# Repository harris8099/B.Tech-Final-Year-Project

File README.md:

# ESP32 Smart Motor Monitor — PCB Design

> KiCad schematic and PCB layout for an ESP32-based industrial motor monitoring and protection system.

---

## Quick Links

| Resource | Link |
|---|---|
| 🌐 Live cloud dashboard | [motor-frontend-psi.vercel.app](https://motor-frontend-psi.vercel.app/) |
| 🖥️ ESP32 local website (demo) | [harris8099.github.io/Motor-Website](https://harris8099.github.io/Motor-Website/index.html) |
| 📦 ESP32 firmware (this repo) | [github.com/harris8099/Final-Year-Project](https://github.com/harris8099/Final-Year-Project) |
| 🎓 PCB schematic and layout | [github.com/harris8099/B.Tech-Final-Year-Project](https://github.com/harris8099/B.Tech-Final-Year-Project) |
| 🖼️ Frontend repository | [github.com/harris8099/Motor-frontend](https://github.com/harris8099/Motor-frontend) |
| ⚙️ Backend repository | [github.com/harris8099/Motor-backend](https://github.com/harris8099/Motor-backend) |
| 📐 Project diagrams & architecture | [github.com/harris8099/Motor-project-Diagram](https://github.com/harris8099/Motor-project-Diagram) |
| 📱 Alternative Bluetooth approach | [harris8099.github.io/Bluetooth-Motor-app](https://harris8099.github.io/Bluetooth-Motor-app/) |

---

## Schematic Overview

Motor Connector Pinout

ADXL345 Sensitivity Reference

## Project Files

| File | Description |
|---|---|
| `ESP32_Smart_Motor_Project.kicad_sch` | Main schematic |
| `overall.kicad_sch` | Top-level/hierarchical schematic |
| `ESP32_Smart_Motor_Project.kicad_pcb` | PCB layout |
| `ESP32_Smart_Motor_Project.kicad_pro` | KiCad project file |
| `Symbol_Lib.kicad_sym` | Custom component symbol library |
| `sch.pdf` | Schematic PDF export |
| `Components_Links.xlsx` | Full BOM with supplier links |
| `ESP32.jpg` | ESP32 module reference image |
| `MOTOR Pins.png` | Motor connector pinout reference |
| `Vibration sensitivity.png` | ADXL345 sensitivity reference |
| `pcbway_production/` | Gerber files for PCB fabrication (PCBWay) |
| `plots/` | Schematic and layout plot exports |
| `Datasheet/` | Component datasheets |

---

## Schematic Overview

The schematic is divided into functional blocks:

### 1. Microcontroller — ESP32-WROOM-32
- Dual-core Xtensa LX6 @ 240 MHz
- 4MB Flash, 520KB SRAM
- On-board Wi-Fi 802.11 b/g/n
- USB-to-UART via CP2102/CH340 for programming and debug
- 3.3V operation with on-board LDO

### 2. Power Supply
- Input: 5V DC from external adapter or USB
- ESP32 powered via 3.3V LDO (AMS1117-3.3 or equivalent)
- Decoupling capacitors on all supply rails (100nF ceramic + 10µF electrolytic)
- Separate power domains for analog sensors and digital logic

### 3. PZEM-004T v3.0 — Power Measurement
- Interface: UART2 (TX → GPIO17, RX → GPIO16)
- Measures: Voltage (80–260V AC), Current (0–100A), Active Power, Energy (kWh), Frequency, Power Factor
- CT (current transformer) clamp around motor live wire
- Isolated from ESP32 logic via UART optocoupler or direct UART (module has internal isolation)
- Baud rate: 9600, 8N1

### 4. DS18B20 — Temperature Sensor
- Interface: 1-Wire (single GPIO)
- 4.7kΩ pull-up resistor on data line to 3.3V (**required**)
- Measures motor winding temperature: –55°C to +125°C, ±0.5°C accuracy
- Waterproof probe variant recommended for motor surface mounting

### 5. ADXL345 — Vibration / Acceleration Sensor
- Interface: I2C (SDA, SCL)
- I2C address: 0x53 (SDO pulled low) or 0x1D (SDO high)
- 4.7kΩ pull-up resistors on SDA and SCL lines
- Range: ±16g, Resolution: 3.9mg/LSB at full range
- Tap detection configured via firmware (threshold, duration, axes)
- Decoupling: 100nF on VCC pin

### 6. Hall Effect Sensor — RPM Measurement
- Interface: GPIO (interrupt-driven)
- GPIO5 configured as input with interrupt on rising edge
- Magnet mounted on motor shaft; sensor detects each revolution
- Pull-up resistor on signal line
- 100nF ceramic capacitor from signal to GND for EMI suppression

### 7. Relay Module — Motor Contactor
- Interface: GPIO (active-low)
- Drives motor contactor coil via relay
- Flyback diode (1N4007) across relay coil for back-EMF protection
- Optocoupler isolation between ESP32 logic and relay coil circuit
- LED indicator for relay state

### 8. Buzzer — Fault Alert
- Interface: GPIO (PWM capable)
- Active buzzer driven via NPN transistor (BC547 or 2N2222)
- 1kΩ base resistor, 10kΩ pull-down to prevent ghost triggering at boot
- Sounds on fault latch

### 9. TFT Display
- Interface: SPI
- CS, DC, RST, BLK connected to dedicated GPIOs
- Backlight PWM dimming capable
- Displays real-time sensor values and fault status locally

---

## Pin Assignment

| GPIO | Function | Direction | Notes |
|---|---|---|---|
| GPIO5 | Hall sensor | Input (IRQ) | 100nF cap to GND |
| GPIO16 | PZEM004T RX | Input | UART2 |
| GPIO17 | PZEM004T TX | Output | UART2 |
| GPIO21 | I2C SDA | Bidirectional | 4.7kΩ pull-up |
| GPIO22 | I2C SCL | Output | 4.7kΩ pull-up |
| GPIO26 | Relay | Output | Active-low |
| GPIO27 | Buzzer | Output | Via NPN transistor |
| 1-Wire GPIO | DS18B20 | Bidirectional | 4.7kΩ pull-up |
| SPI GPIOs | TFT Display | Output | CS/DC/RST/BLK |
| GPIO36 | TFT Button | Input | menu_next (ADC capable) |
| EN / IO0 | Boot control | — | Boot strapping pins |

---

## PCB Design Notes

### Layer Stack
- **2-layer PCB** (standard FR4, 1.6mm thickness)
- Top layer: signal routing + components
- Bottom layer: ground plane + power traces

### Design Rules
- Minimum trace width: 0.25mm (signal), 1.0mm (power), 2.0mm (5V/relay)
- Minimum clearance: 0.2mm
- Via drill: 0.8mm, via pad: 1.6mm
- Board outline: defined in Edge.Cuts layer

### Layout Guidelines Applied
- ESP32 module antenna area kept clear of copper pours and traces
- PZEM UART traces kept short and away from relay switching traces
- I2C pull-up resistors placed close to SDA/SCL pins
- DS18B20 pull-up resistor placed close to connector
- Relay and motor-side traces physically separated from ESP32 signal area
- Decoupling capacitors placed as close as possible to IC power pins
- Ground plane on bottom layer with stitching vias

### Production Files (pcbway_production/)
Standard Gerber outputs for PCBWay fabrication:
- `*.GTL` — Top copper
- `*.GBL` — Bottom copper
- `*.GTS` — Top solder mask
- `*.GBS` — Bottom solder mask
- `*.GTO` — Top silkscreen
- `*.GBO` — Bottom silkscreen
- `*.GKO` — Board outline
- `*.DRL` — Drill file (Excellon)

---

## Bill of Materials (BOM)

Full BOM with supplier links is in `Components_Links.xlsx`. Key components:

| Ref | Component | Value / Part | Package |
|---|---|---|---|
| U1 | ESP32-WROOM-32 | ESP32-WROOM-32D | Module |
| U2 | PZEM-004T | v3.0 | Module |
| U3 | ADXL345 | ADXL345BCCZ | LGA-14 |
| U4 | DS18B20 | DS18B20 | TO-92 / Probe |
| U5 | Voltage Regulator | AMS1117-3.3 | SOT-223 |
| Q1 | NPN Transistor | BC547 / 2N2222 | TO-92 |
| RL1 | Relay | 5V SPDT 10A | Through-hole |
| D1 | Flyback Diode | 1N4007 | DO-41 |
| R1 | DS18B20 Pull-up | 4.7kΩ | 0402 |
| R2, R3 | I2C Pull-up | 4.7kΩ | 0402 |
| R4 | Buzzer Base | 1kΩ | 0402 |
| R5 | Buzzer Pull-down | 10kΩ | 0402 |
| R6 | Hall Pull-up | 10kΩ | 0402 |
| C1–C5 | Decoupling | 100nF | 0402 |
| C6, C7 | Bulk Decoupling | 10µF | 0805 |
| BZ1 | Buzzer | Active 5V | Through-hole |
| J1 | Motor Connector | Screw terminal 3P | 5.08mm pitch |
| J2 | PZEM Connector | JST/Screw 4P | — |
| J3 | TFT Connector | Pin header 8P | 2.54mm |
| J4 | USB / Power | Micro-USB / DC jack | — |
| HALL1 | Hall Sensor | SS49E / A3144 | TO-92 |
| TFT1 | TFT Display | ST7789 / ILI9341 | Module |

---

## Schematic PDF

See [`sch.pdf`](sch.pdf) for the full schematic with all net labels, component values, and reference designators.

---

## Tools Used

| Tool | Version | Purpose |
|---|---|---|
| KiCad | 7.x / 8.x | Schematic capture + PCB layout |
| PCBWay | — | PCB fabrication |
| KiCad PDF Plotter | — | `sch.pdf` export |

---

## Related Repositories

| Repository | Description |
|---|---|
| [Final-Year-Project](https://github.com/harris8099/Final-Year-Project) | ESP32 firmware (ESP-IDF) |
| [Motor-frontend](https://github.com/harris8099/Motor-frontend) | React cloud dashboard |
| [Motor-backend](https://github.com/harris8099/Motor-backend) | FastAPI + PostgreSQL backend |
| [Motor-project-Diagram](https://github.com/harris8099/Motor-project-Diagram) | System architecture diagrams |

## Live Deployments

| Deployment | URL |
|---|---|
| Cloud dashboard | https://motor-frontend-psi.vercel.app/ |
| ESP32 local website demo | https://harris8099.github.io/Motor-Website/index.html |

---

## Author

**Harshil Suthar**

[LinkedIn](https://www.linkedin.com/in/harshil-suthar-942307249/) · [GitHub](https://github.com/harris8099) · [Portfolio](https://harris8099.github.io/Portfolio-2.0/)

---

*Public Domain (CC0). No warranty expressed or implied.*

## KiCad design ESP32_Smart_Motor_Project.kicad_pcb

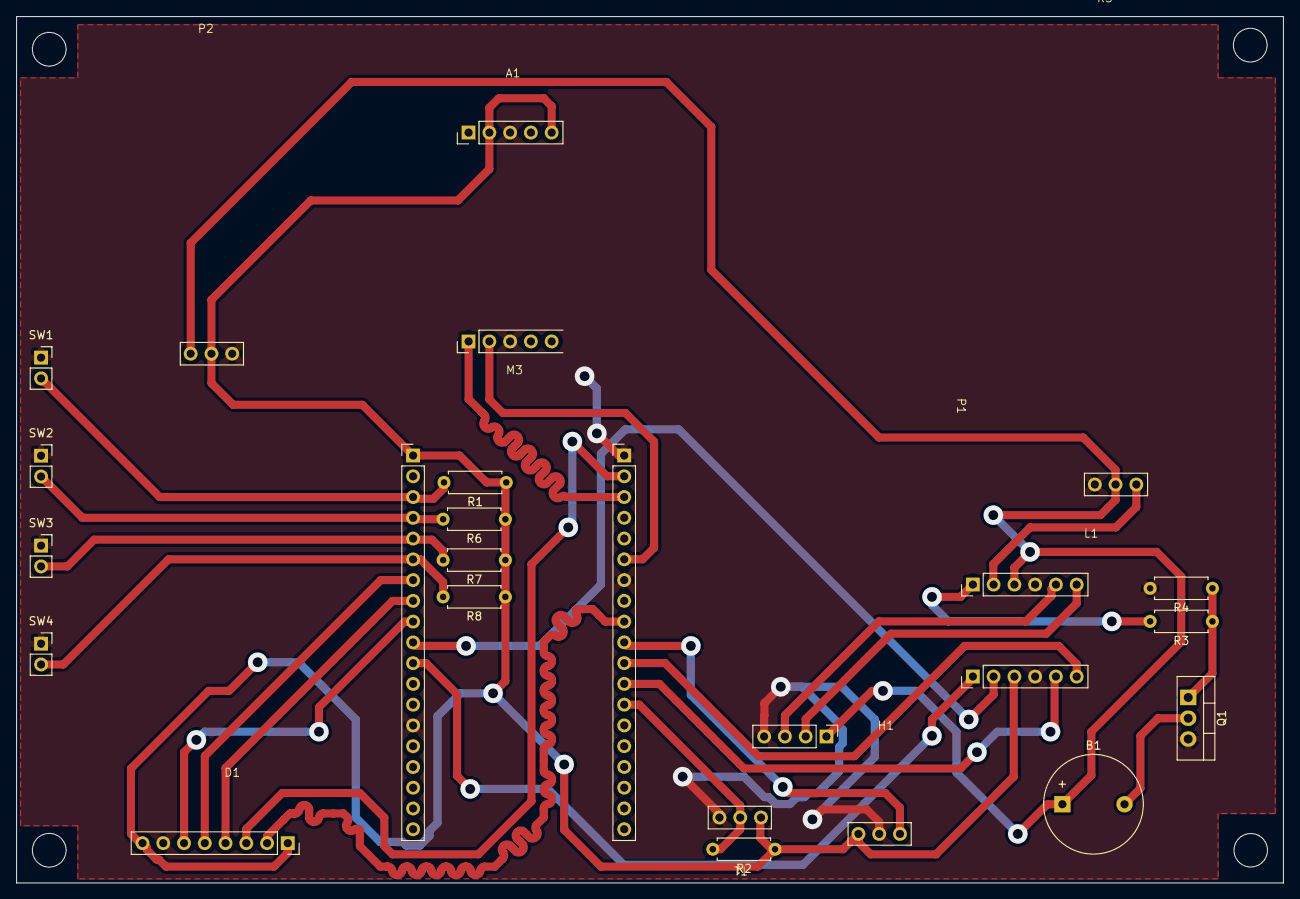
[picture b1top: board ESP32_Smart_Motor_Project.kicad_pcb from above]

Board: 2 copper layers, 155.0 x 106.0 mm, 22 parts (0 on the bottom side), 26 nets.

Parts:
A1: ADXL345
B1: Buzzer_12x9.5RM7.6
D1: TFT_display
H1: Hall_sensor
L1: Logic_convertor
M3: ESP32
P1: PZEM_004T
P2: Power_supply
Q1: IRLZ34N; TO-220-3_Vertical
R1, R4, R6, R7, R8: 10K; R_Axial_DIN0207_L6.3mm_D2.5mm_P7.62mm_Horizontal
R2: 4.7K; R_Axial_DIN0207_L6.3mm_D2.5mm_P7.62mm_Horizontal
R3: 100ohm; R_Axial_DIN0207_L6.3mm_D2.5mm_P7.62mm_Horizontal
R5: Relay
SW1, SW2, SW3, SW4: SW_Push; PinSocket_1x02_P2.54mm_Vertical
T1: DS18B20

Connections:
/3V3: A1.2 (3V3), A1.5 (CS), D1.1 (LED), D1.8 (3.3V), H1.1 (3V3), L1.9 (LV), M3.20 (3.3V), P2.2 (3V3), R1.1, R2.1, R6.1, R7.1, R8.1, T1.1 (3V3)
/5V: B1.1 (SIG), L1.3 (HV), P1.1 (5V), P2.1 (5V), R5.2 (5V)
/GND: A1.3 (GND), A1.8 (SDO), D1.7 (GND), H1.2 (GND), L1.4 (GND), L1.10 (GND), M3.1 (GND), M3.7 (GND), M3.33 (GND), P1.4 (GND), P2.3 (GND), Q1.3 (S), R4.2, R5.1 (GND), SW1.1, SW2.1, SW3.1, SW4.1, T1.3 (GND)
/GPIO4: M3.13 (GPIO4), R2.2, T1.2 (SIG)
/GPIO5: H1.3 (DO), M3.10 (GPIO5)
/GPIO16: L1.11 (LV3), M3.12 (GPIO16)
/GPIO17: L1.12 (LV4), M3.11 (GPIO17)
/GPIO18: D1.2 (SCK), M3.9 (GPIO18)
/GPIO21: A1.7 (SDA), M3.6 (GPIO21)
/GPIO22: A1.6 (SCL), M3.3 (GPIO22)
/GPIO23: D1.3 (SDA), M3.2 (GPIO23)
/GPIO25: D1.6 (CS), M3.28 (GPIO25)
/GPIO26: L1.8 (LV2), M3.29 (GPIO26)
/GPIO27: L1.7 (LV1), M3.30 (GPIO27)
/GPIO32: D1.5 (RESET), M3.26 (GPIO32)
/GPIO33: D1.4 (AO), M3.27 (GPIO33)
/GPIO34: M3.24 (GPIO34), R7.2, SW3.2
/GPIO35: M3.25 (GPIO35), R8.2, SW4.2
/GPIO36: M3.22 (GPIO36), R1.2, SW1.2
/GPIO39: M3.23 (GPIO39), R6.2, SW2.2
/HV1: L1.1 (HV1), R3.2
unnamed: B1.2 (GND), Q1.2 (D)
unnamed: L1.2 (HV2), R5.3 (SIG)
unnamed: L1.5 (HV3), P1.3 (TX)
unnamed: L1.6 (HV4), P1.2 (RX)
unnamed: Q1.1 (G), R3.1, R4.1

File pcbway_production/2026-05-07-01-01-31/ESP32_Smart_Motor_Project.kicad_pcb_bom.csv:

Designator,Quantity,Value,Footprint,Package,MPN,DNP,Mount_Type,Description,KiLib_Generator
A1,1,~,ADXL345,,,,smt,,
B1,1,~,Buzzer_12x9.5RM7.6,,,,tht,,
D1,1,~,TFT_display,,,,smt,,
H1,1,~,Hall_sensor,,,,smt,,
L1,1,~,Logic_convertor,,,,smt,,
M3,1,~,ESP32,,,,smt,,
P1,1,~,PZEM_004T,,,,smt,,
P2,1,~,Power_supply,,,,smt,,
Q1,1,IRLZ34N,TO-220-3_Vertical,,,,tht,"30A Id, 55V Vds, 35mOhm Rds, N-Channel HEXFET Power MOSFET, TO-220AB",package/TO_SOT/THT
"R1, R4, R6, R7, R8",5,10K,R_Axial_DIN0207_L6.3mm_D2.5mm_P7.62mm_Horizontal,,,,tht,Resistor,resistor/THT
R2,1,4.7K,R_Axial_DIN0207_L6.3mm_D2.5mm_P7.62mm_Horizontal,,,,tht,Resistor,resistor/THT
R3,1,100ohm,R_Axial_DIN0207_L6.3mm_D2.5mm_P7.62mm_Horizontal,,,,tht,Resistor,resistor/THT
R5,1,~,Relay,,,,smt,,
"SW1, SW2, SW3, SW4",4,SW_Push,PinSocket_1x02_P2.54mm_Vertical,,,,tht,"Push button switch, generic, two pins",connector/pin_header_socket
T1,1,~,DS18B20,,,,smt,,

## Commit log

2026-02-18 18-02-2026_22:02
2026-04-15 pcb design for smart motor project
2026-04-15 15/04/2026
2026-04-17 minor changes
2026-04-19 19-apr-2026
2026-04-21 make changes to board size
2026-05-06 07-May-26
2026-05-16 Added new sch
2026-05-18 18-05-2026
2026-05-21 Revise README for ESP32 Smart Motor Monitor project
    Updated project title and added detailed project overview, quick links, schematic overview, project files, schematic details, PCB design notes, bill of materials, tools used, related repositories, li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
